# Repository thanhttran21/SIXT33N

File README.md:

# SIXT33N

When I was 4 years old, I told my mom I want to design cars when I'm older. At 22 years old, I created my first voice-controlled robot car in my Designing Information Devices and Systems II (EECS 16B) class. 

SIXT33N was a semester-long project, split up into 4 major components: front-end circuitry, system ID, closed-loop control, and classification.

1. Front-end circuitry consisted of building a low-pass filter in order to attenuate frequencies higher than the normal speaking frequency range. We also built a motor controller circuit using BJTs to act as a switch while also amplifying our 3.3V signal to power our 9V motors. My first try was a terrible nest of wires so I spent an entire evening cleaning up the circuit and making it neat!

2. System ID determines the optimal system operating point because our motors move at different velocities. We used linear regression to model the change in input to change in velocity and the constant offset in velocity. 

3. Closed-loop control allows SIXT33N to drive straight. It takes in input at each timestep and feeds it back into the system. Mathematically, it allows us to pick k-values that set our system's eigenvalues to be stable.

4. Classification lets us give SIXT33N commands to "Go", "Slow down there boy", "Turn left", and "Take a right". We learned how Singular Value Decomposition (SVD) and Principal Component Analysis (PCA) is used decompose our signal into its principal components and then project it onto our matrix of already trained and classified values. This projection allows our system to classify the user's spoken words as any of the 4 commands or as noise.

I learned so much from this project. It was incredibly rewarding to learn the theory in lecture and then directly apply it in hands-on lab. I am very thankful to have such an opportunity. Thank you to my EECS 16B TAs Steven, Martin, and Han. Thank you to my labmates Clay, William, and Kimberly. I'm super excited for what I'll learn in the future!

## [Here](https://drive.google.com/file/d/1dEMNnz95w1OrBTrmgmzlXDoxDUSq32ZZ/view?usp=sharing) is a demo of "Go" for SIXT33N!

My circuit:

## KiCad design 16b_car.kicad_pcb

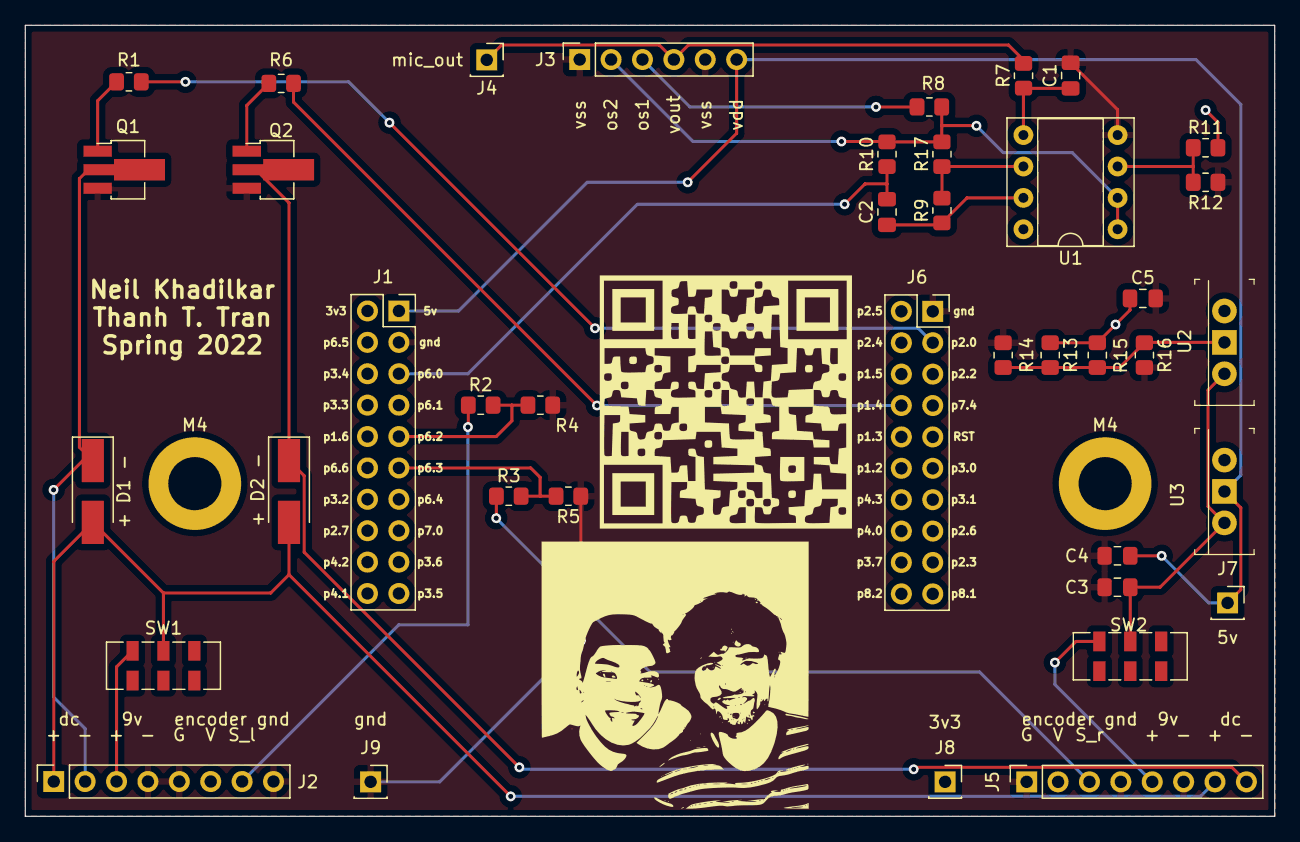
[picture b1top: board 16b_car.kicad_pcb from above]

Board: 2 copper layers, 101.1 x 64.0 mm, 42 parts (0 on the bottom side), 26 nets.

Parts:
+ D1 -, + D2 -: DIODE; D_SMA_Handsoldering
C1, C2, C3, C4: 100 nF; C_0805_2012Metric_Pad1.18x1.45mm_HandSolder
C5: 10 uF; C_0805_2012Metric_Pad1.18x1.45mm_HandSolder
J1, J6: Conn_02x10_Odd_Even; PinSocket_2x10_P2.54mm_Vertical
J2, J5: Conn_01x08_Female; PinSocket_1x08_P2.54mm_Vertical
J3: Conn_01x06_Female; PinSocket_1x06_P2.54mm_Vertical
J4, J7, J8, J9: Conn_01x01_Female; PinSocket_1x01_P2.54mm_Vertical
M4, M4#2: MountingHole_4.3mm_M4_DIN965_Pad
Q1, Q2: Q_NPN_BCE; SOT-89-3_Handsoldering
R1, R6, R14: 1.5 kOhms; R_0805_2012Metric_Pad1.20x1.40mm_HandSolder
R2, R3, R9, R13, R15, R17: 1 kOhms; R_0805_2012Metric_Pad1.20x1.40mm_HandSolder
R4, R5, R16: 2 kOhms; R_0805_2012Metric_Pad1.20x1.40mm_HandSolder
R7: 40 kOhms; R_0805_2012Metric_Pad1.20x1.40mm_HandSolder
R8, R10: 100 kOhms; R_0805_2012Metric_Pad1.20x1.40mm_HandSolder
R11, R12: 10 kOhms; R_0805_2012Metric_Pad1.20x1.40mm_HandSolder
SW1, SW2: SW_DIP_x01; SW_DPDT_CK_JS202011JCQN
U1: LM6482IN/NOPB; lm6482_pdip
U2, U3: LM317T; TO-220-3

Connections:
3.3V: C5.1, J2.6, J5.2, J8.1, R11.2, R13.1, R15.1, U1.8, U2.3 (OUT)
5V: C4.1, J1.1, J3.6, J7.1, U3.2 (3)
9v +l: J2.3, SW1.1
9v +r: J5.5, SW2.1
GND: C1.2, C3.2, C4.2, C5.2, J1.3, J2.4, J2.5, J2.8, J3.1, J3.5, J5.1, J5.4, J5.6, J6.1, J9.1, Q1.3 (E), Q2.3 (E), R4.1, R5.1, R12.1, R14.2, R16.2, U1.4
HALF_RAIL: J3.2, R8.2, R10.2, R17.2, U1.1, U1.2
MIC_OUT: J3.4, J4.1, R7.2
unnamed: C1.1, R7.1, U1.5
unnamed: C2.1, R9.1, U1.7
unnamed: C3.1, SW2.2, U2.1 (IN), U3.1 (IN)
unnamed: Q1.1 (B), R1.2
unnamed: Q2.1 (B), R6.2
unnamed: R11.1, R12.2, U1.3
unnamed: R13.2, R14.1, R15.2, R16.1, U2.2 (ADJ)
unnamed: R9.2, R17.1, U1.6
OS1: J3.3, R8.1
P1.4: J6.8, R6.1
P2.0: J6.3, R1.1
P6.0: C2.2, J1.5, R10.1
P6.2: J1.9, R2.2, R4.2
P6.3: J1.11, R3.2, R5.2
Sl: J2.7, R2.1
Sr: J5.3, R3.1
dc +l: + D1 -.2 (A), + D2 -.2 (A), J2.1, J5.7, SW1.2
dc -l: + D1 -.1 (K), J2.2, Q1.2 (C)
dc -r: + D2 -.1 (K), J5.8, Q2.2 (C)

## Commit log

2022-04-01 motor circuit complete
2022-04-06 regulator circuits added to schematic
2022-04-06 finished the schematic for everything. added annotations and component values. TODO: check ERC with TAs
2022-04-08 footprints added
2022-04-09 started layout
2022-04-15 schematic done, some routing done
2022-04-15 0 errors, 0 warnings
2022-04-15 ready for submission
2022-04-18 ready for ppt
2022-04-18 ready for documentation
